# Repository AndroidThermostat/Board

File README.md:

Android Thermostat Board
========================

Circuit board design files for Android Thermostat.

**Important** Make sure the board design files you use match the revision number on the assembly instructions.  The current release designs are Revision A.

License
-------

CERN OPEN HARDWARE LICENCE v1.1

Preamble

Through this CERN Open Hardware Licence ("CERN OHL") version 1.1, the
Organization wishes to disseminate its hardware designs (as published
on http://www.ohwr.org/) as widely as possible, and generally to
foster collaboration among public research hardware designers.  The
CERN OHL is copyright of CERN. Anyone is welcome to use the CERN OHL,
in unmodified form only, for the distribution of his own Open Hardware
designs. Any other right is reserved.  

1 Definitions

In this Licence, the following terms have the following meanings:

Licence means this CERN OHL.  

Documentation means schematic diagrams, designs, circuit or circuit
board layouts, mechanical drawings, flow charts and descriptive text,
and other explanatory material that is explicitly stated as being made
available under the conditions of this Licence. The Documentation may
be in any medium, including but not limited to computer files and
representations on paper, film, or any other media.  

Product means either an entire, or any part of a, device built using
the Documentation or the modified Documentation.  

Licensee means any natural or legal person exercising rights under
this Licence.  

Licensor means any natural or legal person that creates or modifies
Documentation and subsequently communicates to the public and/ or
distributes the resulting Documentation under the terms and conditions
of this Licence.  

A Licensee may at the same time be a Licensor, and vice versa.

2 Applicability

2.1 This Licence governs the use, copying, modification, communication
to the public and distribution of the Documentation, and the
manufacture and distribution of Products. By exercising any right
granted under this Licence, the Licensee irrevocably accepts these
terms and conditions.  

2.2 This Licence is granted by the Licensor directly to the Licensee,
and shall apply worldwide and without limitation in time. The Licensee
may assign his licence rights or grant sub-licences.  

2.3 This Licence does not apply to software, firmware, or code loaded
into programmable devices which may be used in conjunction with the
Documentation, the modified Documentation or with Products. The use of
such software, firmware, or code is subject to the applicable licence
terms and conditions.  

3 Copying, modification, communication to the public and distribution
of the Documentation

3.1 The Licensee shall keep intact all copyright and trademarks
notices and all notices that refer to this Licence and to the
disclaimer of warranties that is included in the Documentation. He
shall include a copy thereof in every copy of the Documentation or, as
the case may be, modified Documentation, that he communicates to the
public or distributes.

3.2 The Licensee may use, copy, communicate to the public and
distribute verbatim copies of the Documentation, in any medium,
subject to the requirements specified in section 3.1.

3.3 The Licensee may modify the Documentation or any portion
thereof. The Licensee may communicate to the public and distribute the
modified Documentation (thereby in addition to being a Licensee also
becoming a Licensor), always provided that he shall: 
a. comply with section 3.1;
b. cause the modified Documentation to carry prominent notices stating
that the Licensee has modified the Documentation, with the date and
details of the modifications;
c. license the modified Documentation under the terms and conditions
of this Licence or, where applicable, a later version of this Licence
as may be issued by CERN; and
d. send a copy of the modified Documentation to all Licensors that
contributed to the parts of the Documentation that were modified, as
well as to any other Licensor who has requested to receive a copy of
the modified Documentation and has provided a means of contact with
the Documentation.

3.4 The Licence includes a licence to those patents or registered
designs that are held by the Licensor, to the extent necessary to make
use of the rights granted under this Licence. The scope of this
section 3.4 shall be strictly limited to the parts of the
Documentation or modified Documentation created by the Licensor.

4 Manufacture and distribution of Products

4.1 The Licensee may manufacture or distribute Products always
provided that the Licensee distributes to each recipient of such
Products a copy of the Documentation or modified Documentation, as
applicable, and complies with section 3.

4.2 The Licensee is invited to inform in writing any Licensor who has
indicated its wish to receive this information about the type,
quantity and dates of production of Products the Licensee has (had)
manufactured.

5 Warranty and liability

5.1 DISCLAIMER  The Documentation and any modified Documentation are
provided "as is" and any express or implied warranties, including, but
not limited to, implied warranties of merchantability, of satisfactory
quality, and fitness for a particular purpose or use are disclaimed in
respect of the Documentation, the modified Documentation or any
Product. The Licensor makes no representation that the Documentation,
modified Documentation, or any Product, does or will not infringe any
patent, copyright, trade secret or other proprietary right. The entire
risk as to the use, quality, and performance of a Product shall be
with the Licensee and not the Licensor. This disclaimer of warranty is
an essential part of this Licence and a condition for the grant of any
rights granted under this Licence. The Licensee warrants that it does
not act in a consumer capacity.

5.2 LIMITATION OF LIABILITY  The Licensor shall have no liability for
direct, indirect, special, incidental, consequential, exemplary,
punitive or other damages of any character including, without
limitation, procurement of substitute goods or services, loss of use,
data or profits, or business interruption, however caused and on any
theory of contract, warranty, tort (including negligence), product
liability or otherwise, arising in any way in relation to the
Documentation, modified Documentation and/or the use, manufacture or
distribution of a Product, even if advised of the possibility of such
damages, and the Licensee shall hold the Licensor(s) free and harmless
from any liability, costs, damages, fees and expenses, including
claims by third parties, in relation to such use.

6 General

6.1 The rights granted under this Licence do not imply or represent
any transfer or assignment of intellectual property rights to the
Licensee.

6.2 The Licensee shall not use or make reference to any of the names,
acronyms, images or logos under which the Licensor is known, save in
so far as required to comply with section 3. Any such permitted use or
reference shall be factual and shall in no event suggest any kind of
endorsement by the Licensor or its personnel of the modified
Documentation or any Product, or any kind of implication by the
Licensor or its personnel in the preparation of the modified
Documentation or Product.

6.3 CERN may publish updated versions of this Licence which retain the
same general provisions as this version, but differ in detail so far
this is required and reasonable. New versions will be published with a
unique version number.

6.4 This Licence shall terminate with immediate effect, upon written
notice and without involvement of a court if the Licensee fails to
comply with any of its terms and conditions, or if the Licensee
initiates legal action against Licensor in relation to this
Licence. Section 5 shall continue to apply.

6.5 Except as may be otherwise agreed with the Intergovernmental
Organization, any dispute with respect to this Licence involving an
Intergovernmental Organization shall, by virtue of the latter's
Intergovernmental status, be settled by international arbitration. The
arbitration proceedings shall be held at the place where the
Intergovernmental Organization has its seat. The arbitral award shall
be final and binding upon the parties, who hereby expressly agree to
renounce any form of appeal or revision.

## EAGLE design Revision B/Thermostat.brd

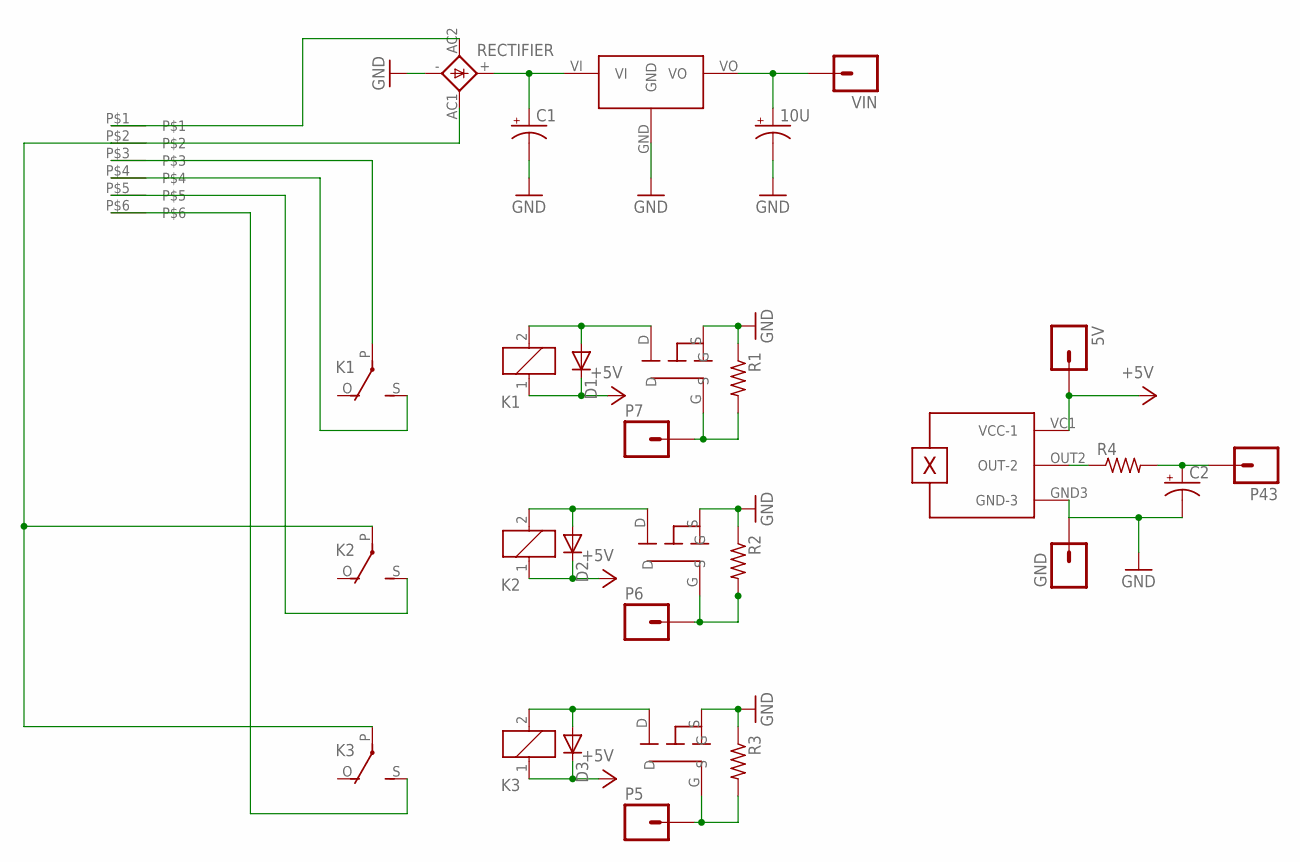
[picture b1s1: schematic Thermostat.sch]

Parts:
5V: M01PTH; 1X01
10U: CAP_POLPTH2; CPOL-RADIAL-10UF-25V
C1: CPOL-USE5-10.5; E5-10,5
C2: CPOL-USE2-5; E2-5
D1, D2, D3: 1N4446; DO35-10
GND: M01PTH; 1X01
K1, K2, K3: G5LE
P5, P6, P7, P43: M01PTH; 1X01
R1, R2, R3, R4: R-US_0204/7; 0204/7
RECTIFIER: GBU4; GBU4S
U$1: TMP36
U$2: V715W-500R; SWITCHINGREGULATOR
U$3: PHOENIX-651-1935200; PHOENIX_E_5MM_6PIN
U$4, U$5, U$6: TRANSISTOR
VIN: M01PTH; 1X01

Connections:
+5V: 5V.1, D1.C, D2.C, D3.C, K1.1, K2.1, K3.1, U$1.VC1 (VCC-1); also elsewhere on the board
GND: 10U.2 (-), C1.-, C2.-, GND.1, R1.1, R2.1, R3.1, RECTIFIER.-, U$1.GND3 (GND-3), U$2.GND, U$4.S, U$5.S, U$6.S; also elsewhere on the board
unnamed: K1.P, U$3.P$3
unnamed: P6.1, R2.2, U$5.G
unnamed: D2.A, K2.2, U$5.D
unnamed: C2.+, P43.1, R4.2
unnamed: R4.1, U$1.OUT2 (OUT-2)
unnamed: P7.1, R1.2, U$6.G
unnamed: D1.A, K1.2, U$6.D
unnamed: K2.P, K3.P, RECTIFIER.AC1 (AC2), U$3.P$2
unnamed: 10U.1 (+), U$2.VO, VIN.1
unnamed: K3.S, U$3.P$6
unnamed: K1.S, U$3.P$4
unnamed: K2.S, U$3.P$5
unnamed: P5.1, R3.2, U$4.G
unnamed: D3.A, K3.2, U$4.D
unnamed: RECTIFIER.AC2 (AC1), U$3.P$1
unnamed: C1.+, RECTIFIER.+, U$2.VI

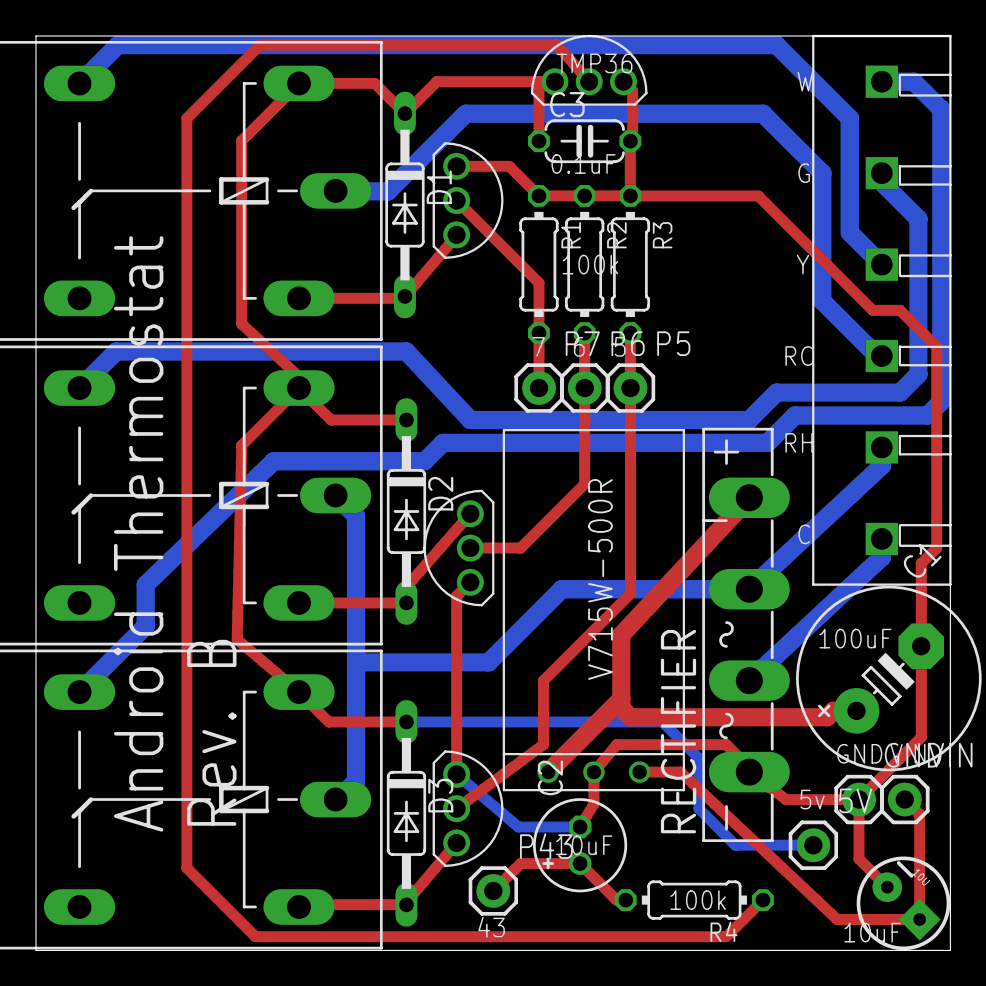
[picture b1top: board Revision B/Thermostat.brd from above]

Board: 2 copper layers, 50.8 x 50.8 mm, 28 parts (0 on the bottom side), 18 nets.

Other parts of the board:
C3: C050-024X044

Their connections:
+5V: C3.1; also elsewhere on the board
GND: C3.2; also elsewhere on the board

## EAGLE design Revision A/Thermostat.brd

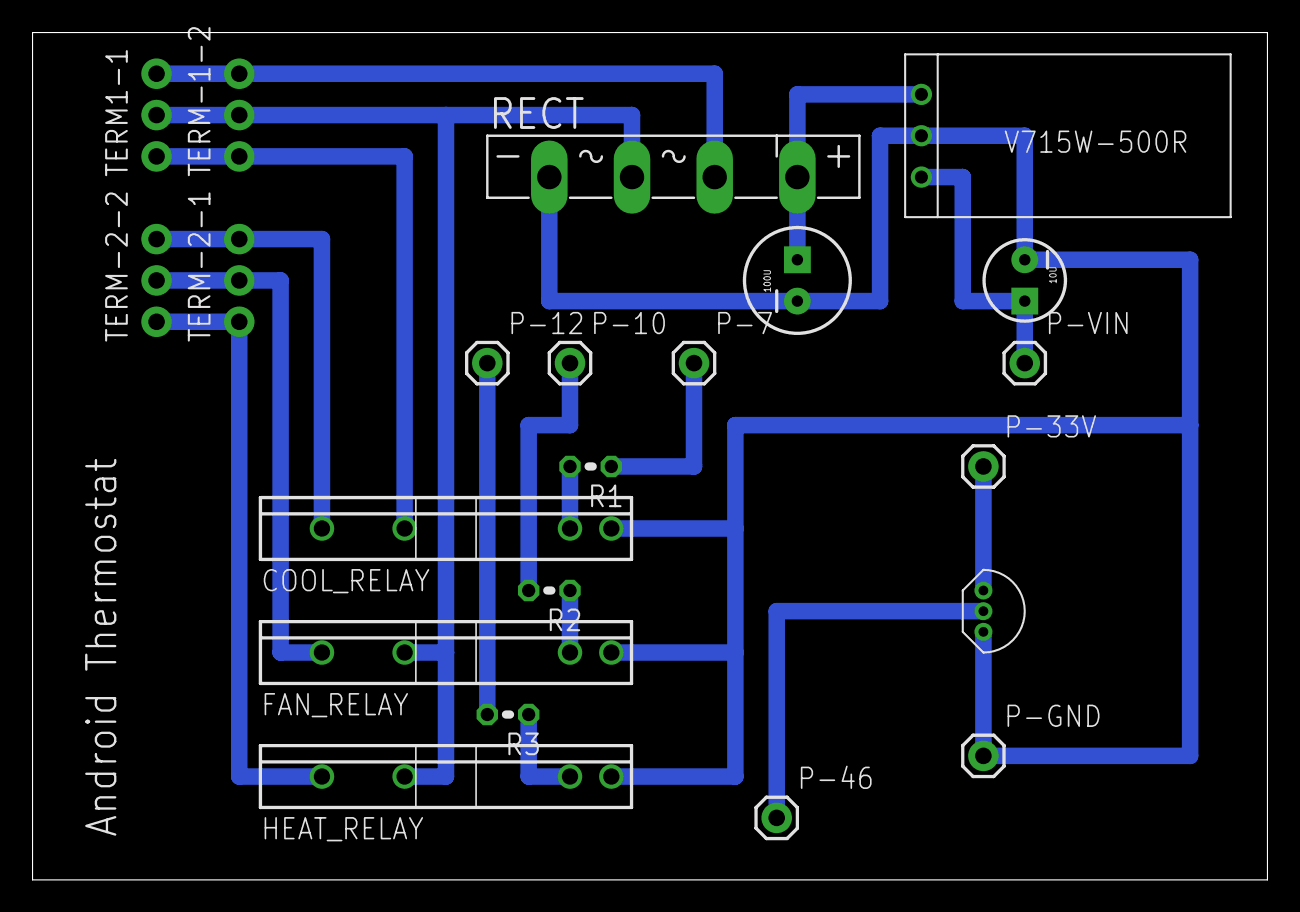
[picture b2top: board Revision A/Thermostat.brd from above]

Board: 2 copper layers, 75.9 x 52.1 mm, 22 parts (0 on the bottom side), 17 nets.

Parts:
10U: CPOL-RADIAL-10UF-25V
100U: CPOL-RADIAL-100UF-25V
COOL_RELAY: S101T01; S102T0X
FAN_RELAY: S101T01; S102T0X
HEAT_RELAY: S101T01; S102T0X
P-7, P-10, P-12, P-33V, P-46: M01PTH; 1X01
P-GND: M01PTH; 1X01
P-VIN: M01PTH; 1X01
R1, R2, R3: 0204V
RECT: GBU4S
TERM1-1: 1X03_NO_SILK
TERM-1-2, TERM-2-1, TERM-2-2: 1X03_NO_SILK
U$1: TMP36
U$2: V715W-500R; SWITCHINGREGULATOR

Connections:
GND: 10U.2, 100U.2, COOL_RELAY.4, FAN_RELAY.4, HEAT_RELAY.4, P-GND.1, RECT.-, U$1.GND-3, U$2.GND
unnamed: COOL_RELAY.2, TERM1-1.1, TERM-1-2.1
unnamed: HEAT_RELAY.3, R3.1
unnamed: RECT.AC1, TERM1-1.3, TERM-1-2.3
unnamed: P-7.1, R1.1
unnamed: P-46.1, U$1.DATA-2
unnamed: FAN_RELAY.3, R2.1
unnamed: P-10.1, R2.2
unnamed: P-12.1, R3.2
unnamed: COOL_RELAY.3, R1.2
unnamed: 10U.1, P-VIN.1, U$2.VO
unnamed: P-33V.1, U$1.VCC-1
unnamed: 100U.1, RECT.+, U$2.VI
unnamed: HEAT_RELAY.1, TERM-2-1.1, TERM-2-2.1
unnamed: COOL_RELAY.1, TERM-2-1.3, TERM-2-2.3
unnamed: FAN_RELAY.1, TERM-2-1.2, TERM-2-2.2
P2: FAN_RELAY.2, HEAT_RELAY.2, RECT.AC2, TERM1-1.2, TERM-1-2.2

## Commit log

2012-11-22 Initial Checkin
    The Eagle files created by Randy Farmer from the PDF and ExpressPCB
    designs posted at AndroidThermostat.com. The design currently contains
    at least two errors with the wrong type of regulator and temperature
    sensor being shown that will need to be corrected.
2012-11-23 Custom Components
    Designed custom components for the temperature sensor and switching
    regulator. Corrected pin 42 to 46. Corrected some mistakes in the
    schematic and re-arranged it. Rewired the board paths to match the
    original published directions. Have not tested printing or alignment
    yet.
2012-11-25 Fixed Alignment
    Moved all of the components to match the published board. Revision A
    should be complete now.
2012-11-27 Started Revision B
    Started the second revison of the circuit board for the IOIO OTG. The
    main goal for this revision is to get the price down as much as
    possible, which includes shrinking the circuit board from 2x3 to 2x3.
2012-11-27 Added Revision B Parts List
    Added the first draft of which parts will be needed for Revision B
2012-11-28 Added Transistors
    The IOIO can only supply 20ma from the digital pins, so I added
    transistors to feed 5v and switched to the 5v relays.
2012-11-29 Added CERN Open Hardware License
2012-12-01 Finished Board Layout with Transistors
    Changed the transistor symbol.
    Changed wires to routes
    Verified against design rules
    Added top and bottom silk text
2012-12-01 Checked in second lbr file
    GitHub wasn't recognizing the changes so I added a second one for now.
2012-12-01 Updated ReadMe
    Fixed formatting on ReadMe file.
2012-12-02 First Test Print
    Added Labels
    Exported Gerber Files
    Ordered Test Print
    Adjusted borders to exact 2"x2" after ordering the print.
2012-12-06 Added Temperature Sensor Capacitor
    Added a capacitor to pin 4 to smooth out the voltage reading from the
    temperature sensor. I still need to calculate exactly what size that
    capacitor should be.
2012-12-06 Added Temperature Sensor Resistor
    Added a 150k resistor to the temperature sensor to drop the amps to 5uA,
    below the 7uA output of the temperature sensor, in order to allow the
    capacitor to charge.
2012-12-23 Made tweeks after first print
    Moved relay bodies off the board to provide more space.
    Widened holes for temp sensor, transistors, capacitor and terminal
    Spread out components that were overlapping.
    Removed wires crossing low-pass filter.
2013-01-06 Prepared for second print
    Moved components to within spacing tolerances.
    Added and moved labels.
    Ordered second print.
2013-01-24 Moved Temperature Pin
    Moved the temperature sensor input from PIN 4 (digital) to PIN 43
    (analog). This required moving a number of components around on the
    board.
2013-02-10 Moved Rectifier
    On the third print the bridge rectifier was too close to the 100uf
    capacitor. I moved it slightly and had to move the regulator and diodes
    as well.
2013-02-19 Moved Temperature Sensor
    It was too close to the switching regulator which is putting out a lot
    of heat.
2013-03-05 Low-pass filter changes
    Made adjustments to the low-pass filter per suggestions at:
    http://www.reddit.com/r/AndroidThermostat/comments/19ntz4/temp_sensor_filter/
2013-03-06 Added Capacitor
    Added a 0.1uF capacitor between the 5v and GND lines on the temperature
    sensor to help avoid fluctuations.
2013-03-06 Fixed Spacing
    One of the pathways was too close to a plate and failed the validation.
2013-05-17 Temperature Sensor Isolation
    Moved AC relay wires away from the temperature sensor and added a
    cut-out to isolate it from heat generated by the relay.
2013-06-27 Added PDFs
    Added PDF versions of the B1 schematic and board, and the Revision A
    protoboard files that were previously only hosted on the website.

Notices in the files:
parts and their libraries:
SparkFun-Connectors: Licensing: CC v3.0 Share-Alike You are welcome to use this library for commercial purposes.
